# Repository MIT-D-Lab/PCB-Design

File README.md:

# PCB-Design
Various demos for the HD4D class as well as KiCAD libraries and other useful things!

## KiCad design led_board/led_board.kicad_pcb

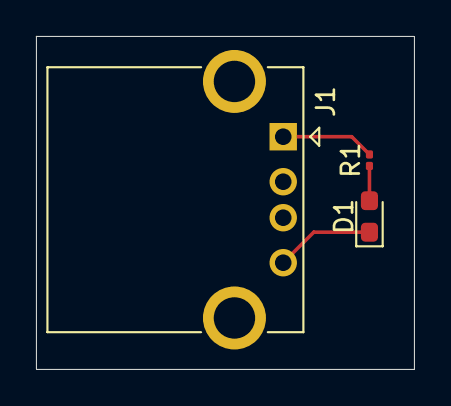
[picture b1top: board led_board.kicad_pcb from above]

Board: 2 copper layers, 21.0 x 18.5 mm, 3 parts (0 on the bottom side), 3 nets.

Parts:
D1: LED; LED_0603_1608Metric_Pad1.05x0.95mm_HandSolder
J1: USB_A; USB_A_CONNFLY_DS1095-WNR0
R1: R; R_0201_0603Metric

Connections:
GND: D1.1 (K), J1.4 (GND), J1.5 (Shield)
unnamed: D1.2 (A), R1.1
unnamed: J1.1 (VBUS), R1.2

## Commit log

2024-09-18 new pcb just dropped
